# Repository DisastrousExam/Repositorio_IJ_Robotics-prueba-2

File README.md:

# Repositorio_IJ_Robotics-prueba-2
**Prueba de repositorio para diseño de pcb**

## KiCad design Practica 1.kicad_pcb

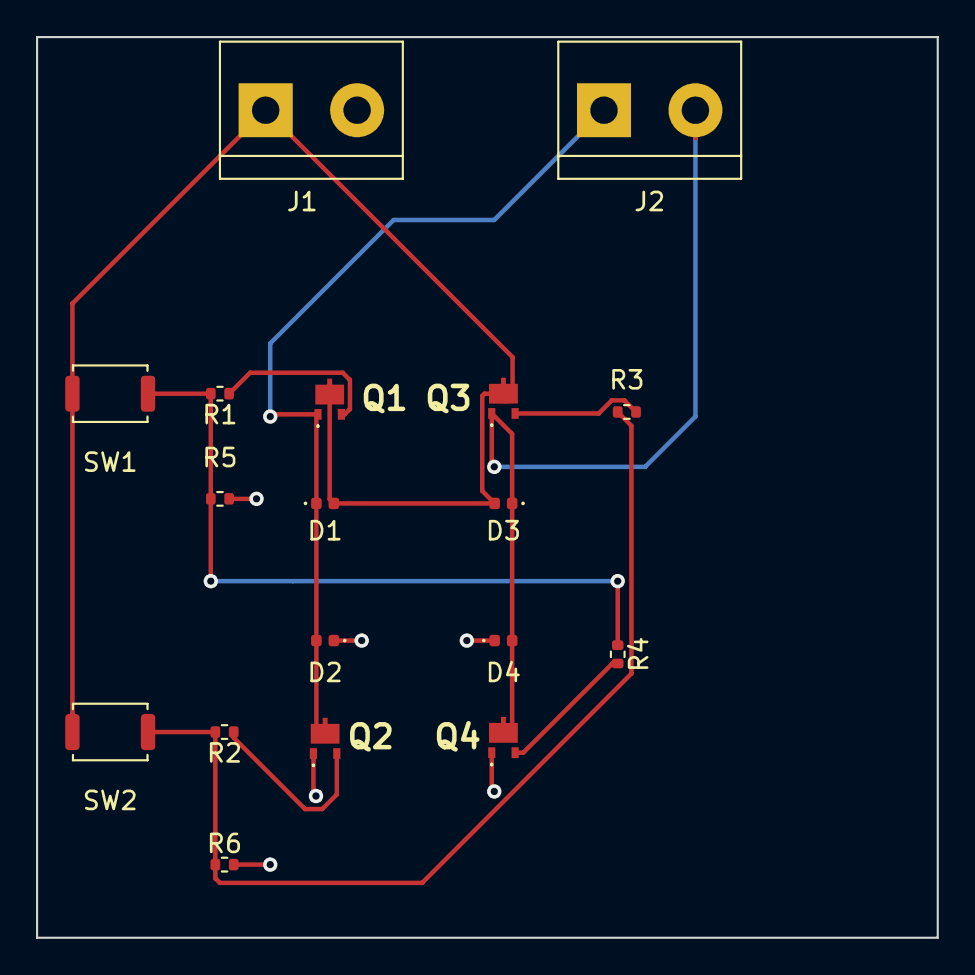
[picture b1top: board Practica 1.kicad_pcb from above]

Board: 2 copper layers, 50.0 x 50.0 mm, 18 parts (0 on the bottom side), 10 nets.

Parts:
D1, D2, D3, D4: DIODE; D_0402_1005Metric
J1, J2: Conn_01x02; TerminalBlock_bornier-2_P5.08mm
Q1, Q2, Q3, Q4: BC107; NSVBCP56MTWG
R1, R2, R3, R4: 32; R_0402_1005Metric
R5, R6: 10k; R_0402_1005Metric
SW1, SW2: SW_Push; SW_Push_SPST_NO_Alps_SKRK

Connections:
+12V: D1.2, D3.2, J1.1, Q1.3, Q3.3, SW1.1, SW2.1
GND: D2.1, D4.1, J1.2, Q2.1, Q4.1, R5.2, R6.2
unnamed: D1.1, D2.2, J2.1, Q1.1, Q2.3
unnamed: D3.1, D4.2, J2.2, Q3.1, Q4.3
unnamed: Q1.2, R1.1
unnamed: Q2.2, R2.1
unnamed: Q3.2, R3.2
unnamed: Q4.2, R4.2
unnamed: R1.2, R4.1, R5.1, SW1.2
unnamed: R2.2, R3.1, R6.1, SW2.2

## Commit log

2025-07-10 prueba de subida de archivos
2025-07-10 cambio de posicion de pines
2025-07-10 Segundo movimiento de etiquetas
2025-07-10 Movimento de etiquetas 3
